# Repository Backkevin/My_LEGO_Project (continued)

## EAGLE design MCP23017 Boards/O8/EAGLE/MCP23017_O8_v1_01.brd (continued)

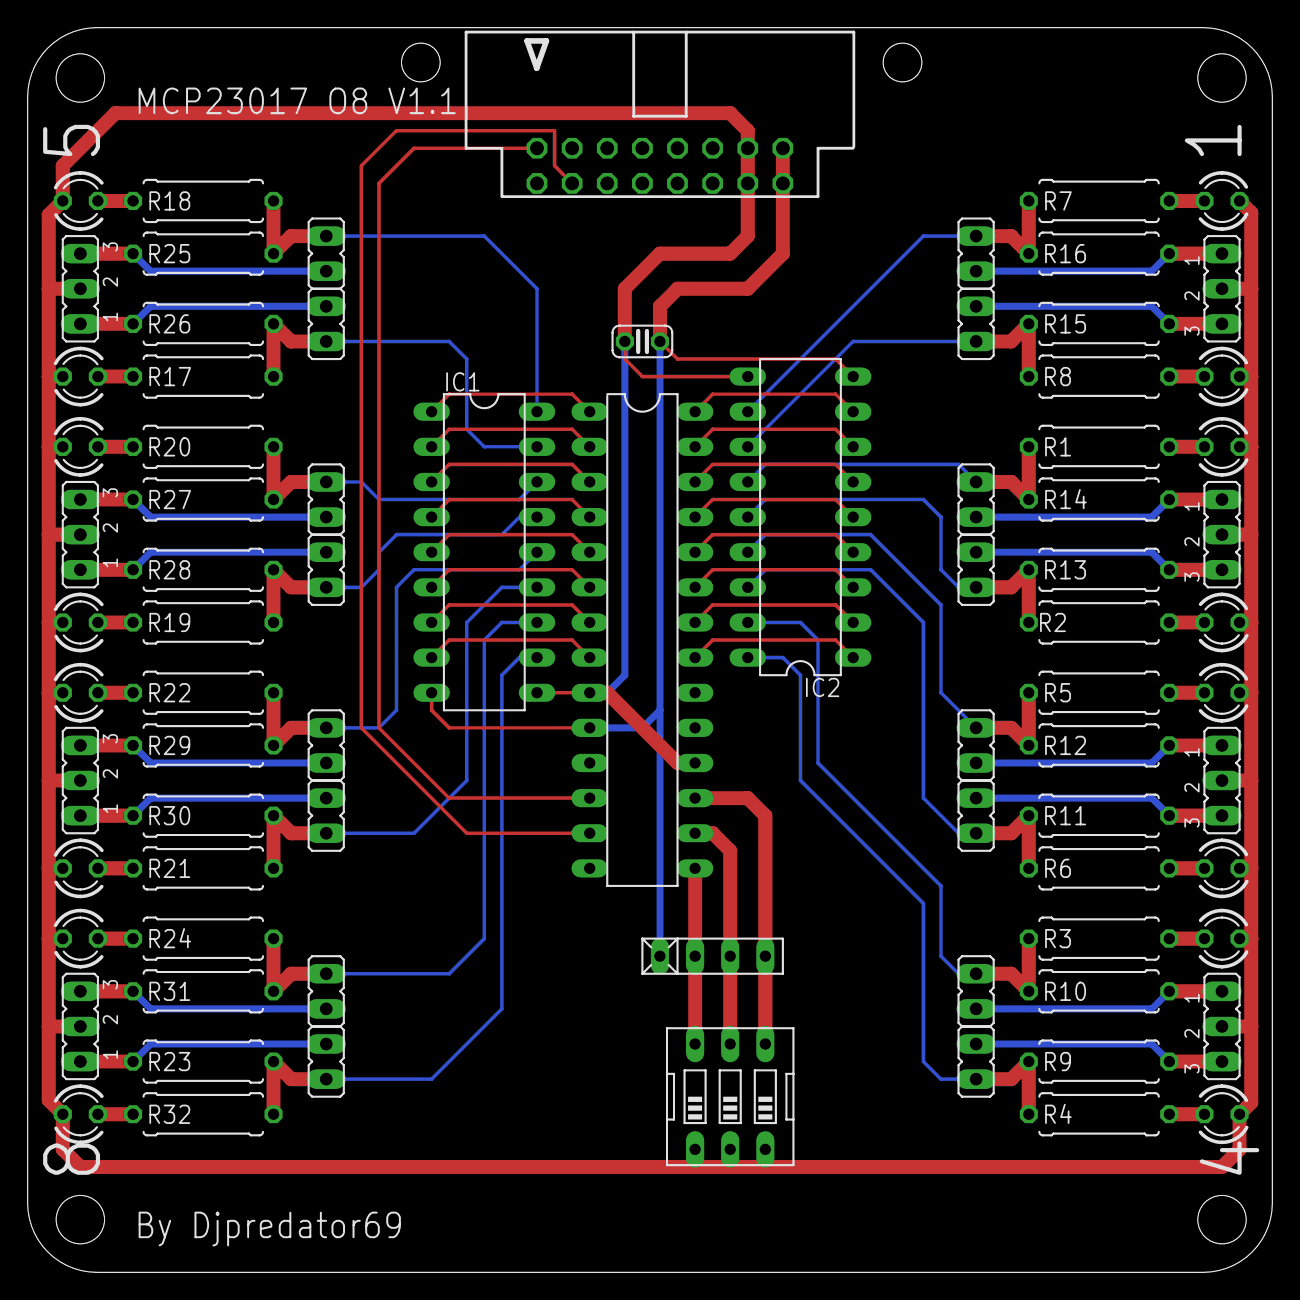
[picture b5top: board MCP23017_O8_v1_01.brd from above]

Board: 2 copper layers, 90.0 x 90.0 mm, 79 parts (0 on the bottom side), 71 nets.

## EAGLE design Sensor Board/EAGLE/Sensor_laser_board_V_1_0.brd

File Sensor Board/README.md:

SENSOR BOARDS
 
-----------------------------------------------------------------
Experimental
-----------------------------------------------------------------

+ Sensor_GP1A57HRJ00F_board_V_1_0
>
-----------------------------------------------------------------
Sensor_TCRT5000_board_V_1_0
>
-----------------------------------------------------------------
+ Sensor_board_V_1_0
>
-----------------------------------------------------------------
+ Sensor_board_2_V_1_0
>
-----------------------------------------------------------------
+ Sensor_laser_board_V_1_0
>
-----------------------------------------------------------------

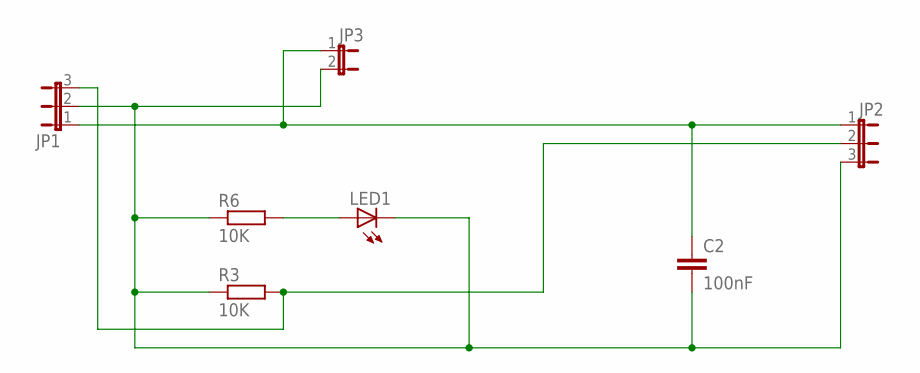
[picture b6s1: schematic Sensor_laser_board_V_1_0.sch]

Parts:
C2: 100nF; C025_050-025X075
JP1, JP2: JP2E; JP2
JP3: JP1E; JP1
LED1: LED3MM
R3, R6: 10K; 0309/10

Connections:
GND: C2.1, JP1.1, JP2.1, JP3.1
unnamed: C2.2, JP1.2, JP2.3, JP3.2, LED1.K (C), R3.1, R6.1
unnamed: LED1.A, R6.2
unnamed: JP1.3, JP2.2, R3.2

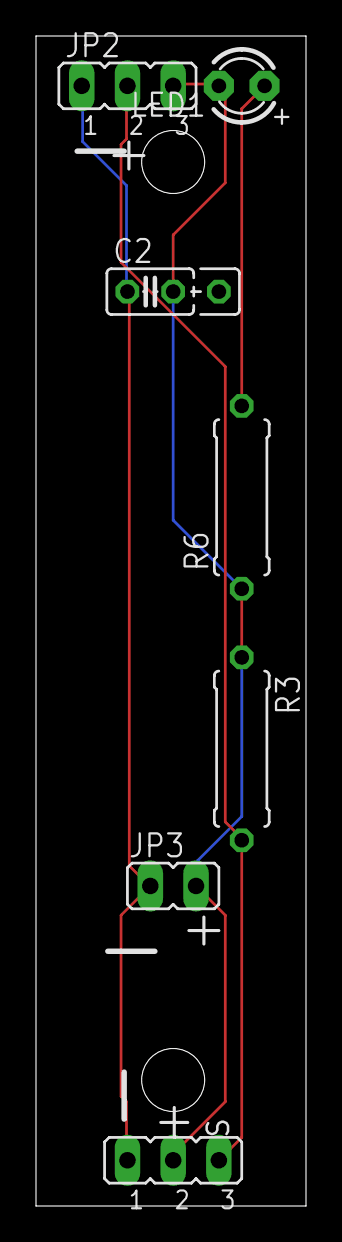
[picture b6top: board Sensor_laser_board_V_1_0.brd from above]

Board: 2 copper layers, 15.0 x 65.0 mm, 7 parts (0 on the bottom side), 4 nets.

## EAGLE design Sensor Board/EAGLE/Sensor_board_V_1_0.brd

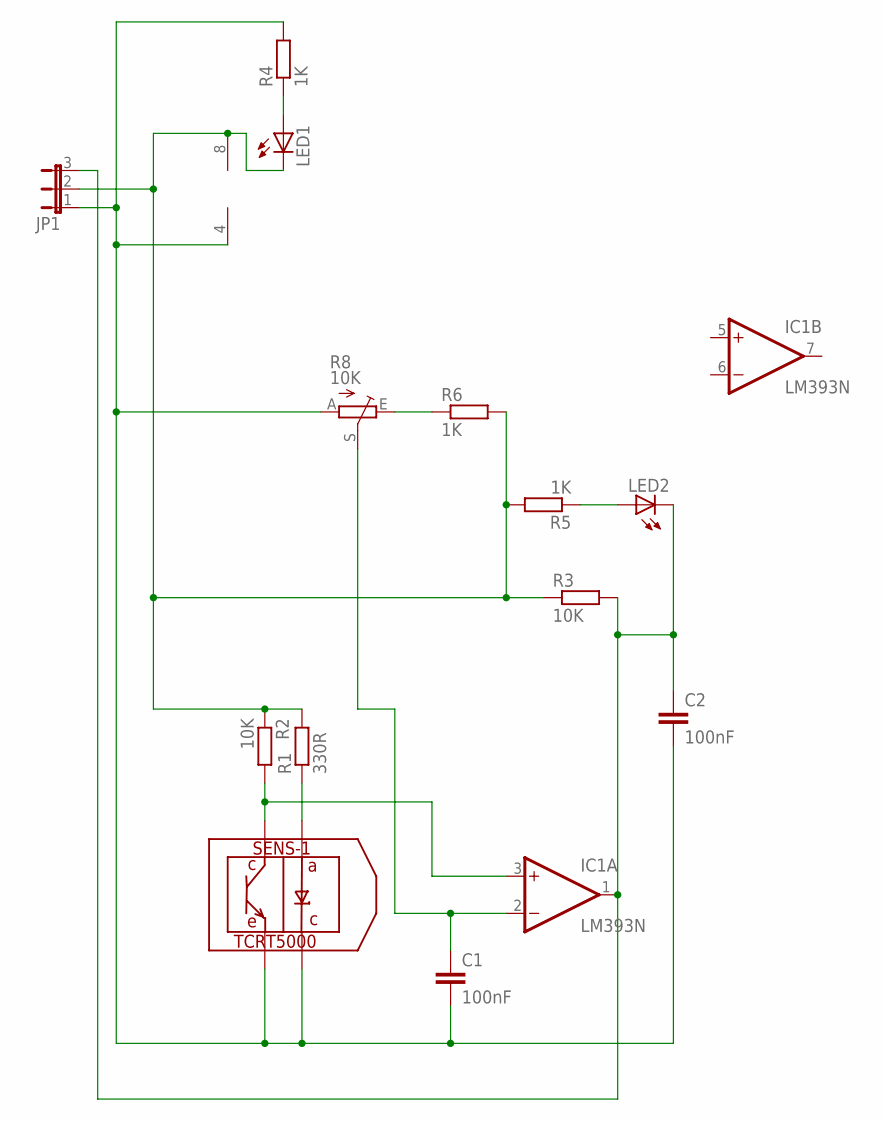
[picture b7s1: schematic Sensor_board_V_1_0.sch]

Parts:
C1, C2: 100nF; C025_050-025X075
IC1: LM393N; DIL08
JP1: JP2E; JP2
LED1, LED2: LED3MM
R1: 330R; 0309/10
R2, R3: 10K; 0309/10
R4, R5, R6: 1K; 0309/10
R8: 10K; B64Y
SENS-1: TCRT5000; 5000

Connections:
unnamed: IC1.8 (V+), JP1.2, LED1.K (C), R1.2, R2.1, R3.1, R5.2, R6.2
unnamed: LED1.A, R4.1
unnamed: C1.2, C2.2, IC1.4 (V-), JP1.1, R4.2, R8.A, SENS-1.P$2, SENS-1.P$4
unnamed: R1.1, SENS-1.P$3
unnamed: IC1.3 (+IN), R2.2, SENS-1.P$1
unnamed: C2.1, IC1.1 (OUT), JP1.3, LED2.K (C), R3.2
unnamed: LED2.A, R5.1
unnamed: R6.1, R8.E
unnamed: C1.1, IC1.2 (-IN), R8.S

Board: 2 copper layers, 14 parts (0 on the bottom side), 9 nets, no tracks yet.

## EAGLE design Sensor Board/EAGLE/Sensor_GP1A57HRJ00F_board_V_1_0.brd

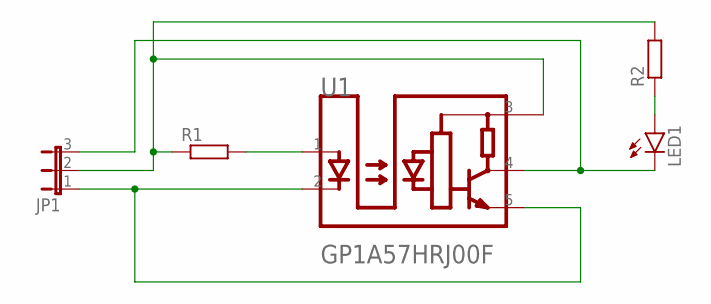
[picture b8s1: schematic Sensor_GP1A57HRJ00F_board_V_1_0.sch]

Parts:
JP1: JP2E; JP2
LED1: LED3MM
R1, R2: R-EU_0309/10; 0309/10
U1: SHARP_GP1A57HRJ00FSHARP_GP1A57HRJ00F_0_0; SHARP_GP1A57HRJ00F_0

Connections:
+5VDC: JP1.2, R1.1, R2.2, U1.3 (VCC)
GND: JP1.1, U1.2 (CATHODE), U1.5 (GND)
unnamed: R1.2, U1.1 (ANODE)
unnamed: LED1.A, R2.1
SIG: JP1.3, LED1.K (C), U1.4 (VO)

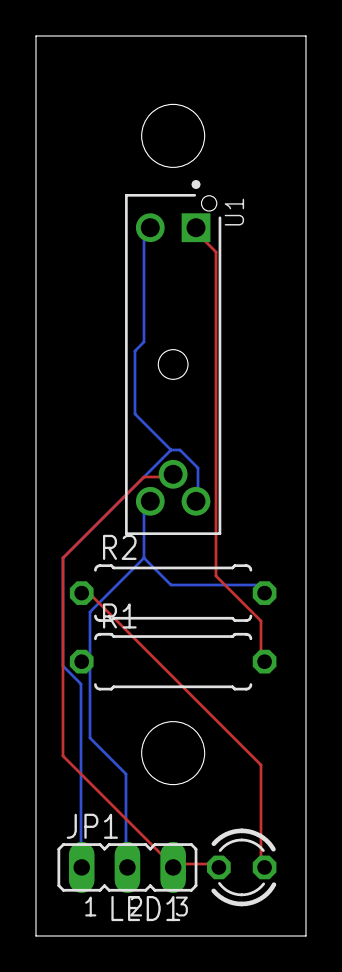
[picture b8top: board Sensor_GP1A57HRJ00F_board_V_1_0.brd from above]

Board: 2 copper layers, 15.0 x 50.0 mm, 5 parts (0 on the bottom side), 5 nets.

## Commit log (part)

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2021-03-13 Create L9110_v1_0.b#1
2021-03-13 Create L9110_v1_0.b#3
2021-03-13 Create L9110_v1_0.b#4
2021-03-13 Create L9110_v1_0.b#2
2021-05-06 Create Sensor_board_2_V_1_1.b#1
